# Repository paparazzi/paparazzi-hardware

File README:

#
#   $Id: README 6372 2010-11-07 00:50:29Z esden $
#   Copyright (C) 2004 Pascal Brisset, Antoine Drouin
#
# This file is part of paparazzi.
#
# paparazzi is free software; you can redistribute it and/or modify
# it under the terms of the GNU General Public License as published by
# the Free Software Foundation; either version 2, or (at your option)
# any later version.
#
# paparazzi is distributed in the hope that it will be useful,
# but WITHOUT ANY WARRANTY; without even the implied warranty of
# MERCHANTABILITY or FITNESS FOR A PARTICULAR PURPOSE.  See the
# GNU General Public License for more details.
#
# You should have received a copy of the GNU General Public License
# along with paparazzi; see the file COPYING.  If not, write to
# the Free Software Foundation, 59 Temple Place - Suite 330,
# Boston, MA 02111-1307, USA.  
# 

License:
--------
All PCB CAD files are released under GNU General Public License version 2 or
newer if not stated otherwise.

Older revisions:
----------------
This is a cleaned up repository that does not contain all the history of the
files. For older revisions please check the SVN repository on Savannah:
http://svn.savannah.nongnu.org/viewvc/paparazzi-hardware/trunk/?root=paparazzi

Techno:
-------
PCBs are 4 layers boards.
  They can be ordered from companies like eurocircuits (www.eurocircuits.com).
  I solder the components with a fine temperatue controlled iron. The IMU board 
  contains BGA gyros which will require some sort hot hot air method.

Tools:
  This files are produced using Eagle (www.cadsoft.de) version 4.11 for Linux.
  gerbmerge (http://claymore.engineer.gvsu.edu/~steriana/Python/gerbmerge/) is a
  free gerber panelisation tool. gerbv (http://gerbv.sourceforge.net) is a free
  gerber viewer. eagle3d ( http://www.matwei.de/doku.php?id=en:eagle3d:eagle3d )
  is a tool that allows generation of povray views of the boards.

Outputs:
  We use the eagle batch CAM processor to generate various outputs.
  type "make gerber" to generate gerber.
  type "make printable" to generate postscript and pdf. 
  they will be put in a printable subdirectory in each subdirectory. 

Directory content:
------------------
panel: 
  Contains configuration files used in conjunction with gerbmerge to produce a pannel
  to be sent to the PCB manufacturer (eurocircuits). A panel is a big PCB containing several smaller PCB.
  It allows you to choose which boards you want for your particular system.

controller: 
  This are the paparazzi controller boards.

sensors:

tools:

lib: 
  contains eagle library parts for components not found in the standard eagle library.

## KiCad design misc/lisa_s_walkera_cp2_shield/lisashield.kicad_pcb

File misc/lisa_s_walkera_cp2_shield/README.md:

This is a prototype. Current status:

* Only connectors are used, the rest is cut off.
* No decent GND connection.
* Polarity of tail rotor is reversed, need to exchange wires in the molex-connector.

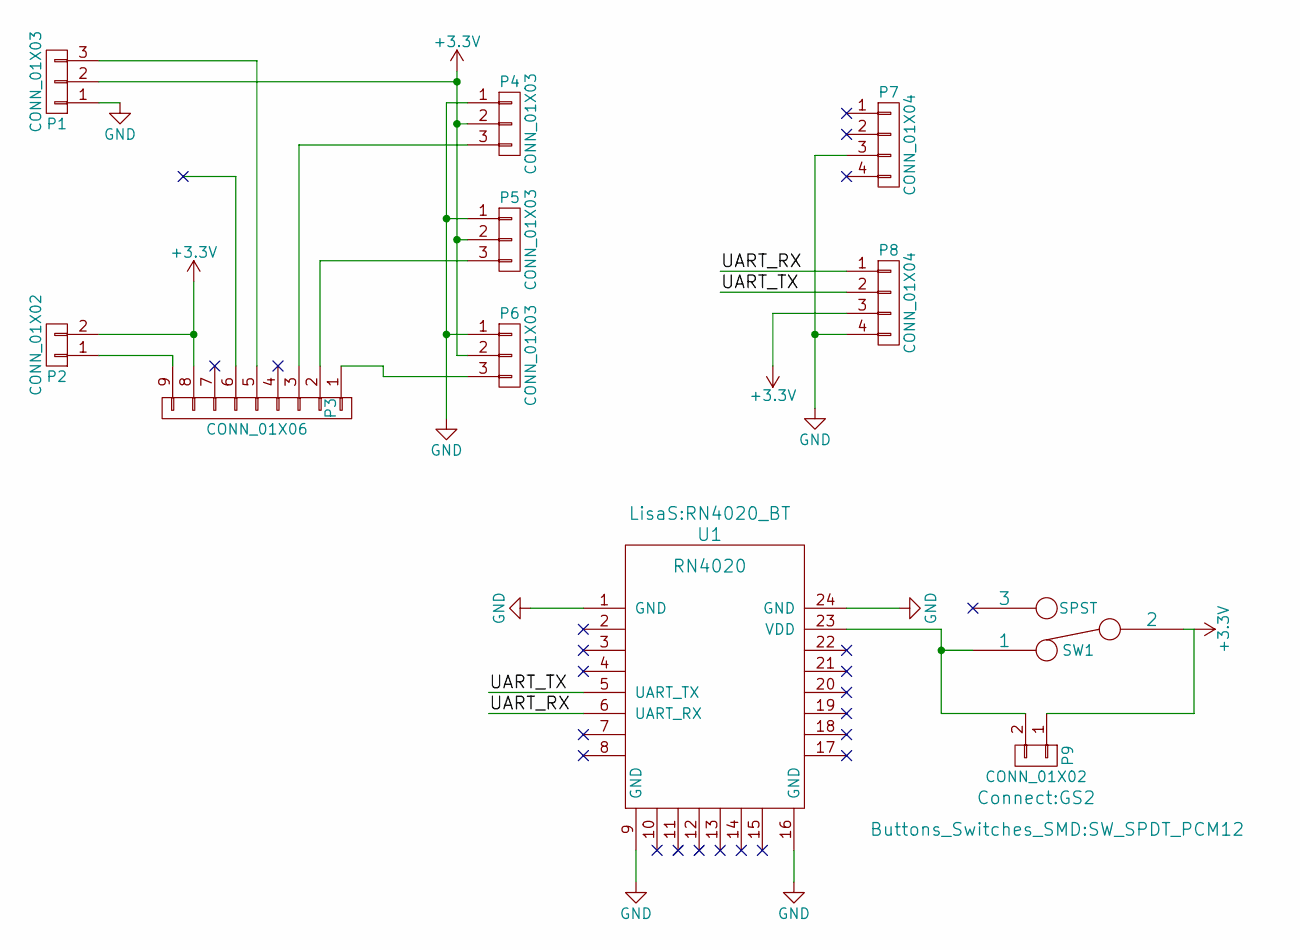
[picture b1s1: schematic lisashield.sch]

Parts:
P1, P4, P5, P6: CONN_01X03; Connector_Molex_PicoBlade_53047-0310
P2: CONN_01X02; Connector_Molex_PicoBlade_53047-0210
P3: CONN_01X06; 9x1_1.27mm
P7, P8: CONN_01X04; 4x1_1.27mm
P9: CONN_01X02; GS2
SW1: SPST; SW_SPDT_PCM12
U1: RN4020; RN4020_BT

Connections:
+3V3: P1.2, P2.2, P3.8, P4.2, P5.2, P6.2, P8.3, P9.1, SW1.2
/UART_RX: P8.1, U1.6 (UART_RX)
/UART_TX: P8.2, U1.5 (UART_TX)
GND: P1.1, P4.1, P5.1, P6.1, P7.3, P8.4, U1.1 (GND), U1.9 (GND), U1.16 (GND), U1.24 (GND)
unnamed: P1.3, P3.5
unnamed: P2.1, P3.9
unnamed: P3.1, P6.3
unnamed: P3.2, P5.3
unnamed: P3.3, P4.3
unnamed: P9.2, SW1.1, U1.23 (VDD)

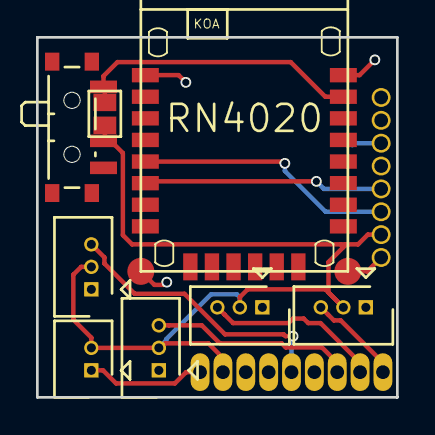
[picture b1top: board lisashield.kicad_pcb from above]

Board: 2 copper layers, 20.0 x 20.0 mm, 11 parts (0 on the bottom side), 10 nets.

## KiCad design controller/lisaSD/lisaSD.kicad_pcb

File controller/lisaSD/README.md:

http://wiki.paparazziuav.org/wiki/SDLogger_SPI_Direct

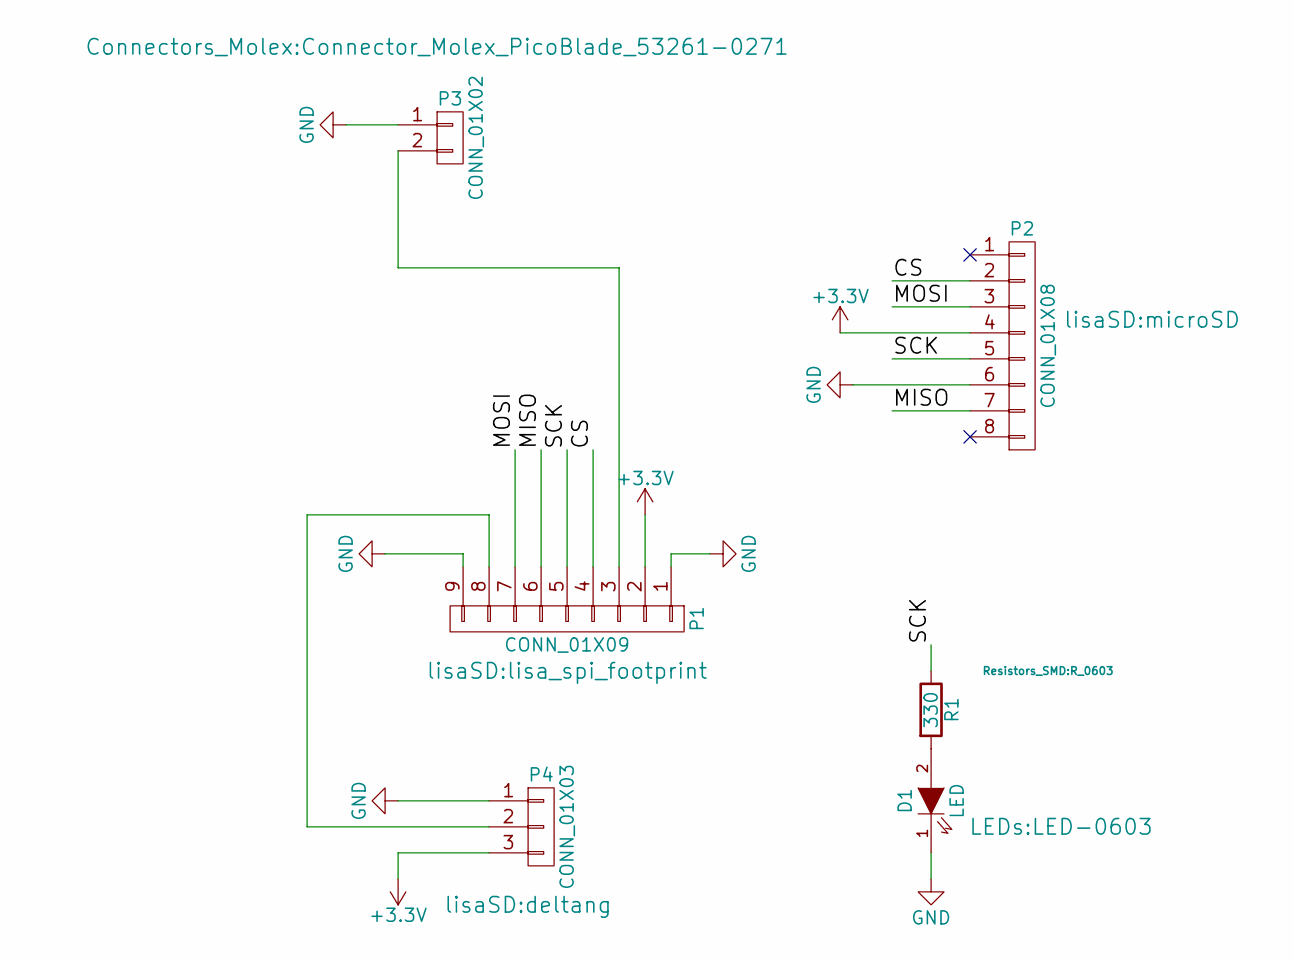
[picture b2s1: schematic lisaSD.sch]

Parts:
D1: LED; LED-0603
P1: CONN_01X09; lisa_spi_footprint
P2: CONN_01X08; microSD
P3: CONN_01X02; Connector_Molex_PicoBlade_53261-0271
P4: CONN_01X03; deltang
R1: 330; R_0603

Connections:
+3V3: P1.2, P2.4, P4.3
/CS: P1.4, P2.2
/MISO: P1.6, P2.7
/MOSI: P1.7, P2.3
/SCK: P1.5, P2.5, R1.1
GND: D1.1 (K), P1.1, P1.9, P2.6, P3.1, P4.1
unnamed: D1.2 (A), R1.2
unnamed: P1.3, P3.2
unnamed: P1.8, P4.2

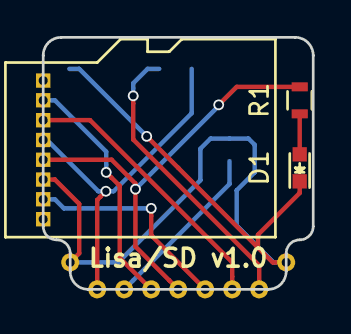
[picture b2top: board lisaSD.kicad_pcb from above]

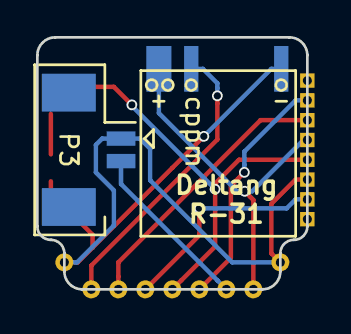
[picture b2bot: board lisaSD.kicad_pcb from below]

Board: 2 copper layers, 15.0 x 14.0 mm, 6 parts (2 on the bottom side), 9 nets.

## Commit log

2011-11-24 Initial commit after a coarce cleanup. For older revisions check the hardware svn repository on Savannah. http://svn.savannah.nongnu.org/viewvc/paparazzi-hardware/trunk/?root=paparazzi
2011-11-24 Reorganized sensor directory a bit.
2011-12-01 Starting work on lia v1.0 controller board.
    It is based on lisa/m and uses throughole 0.1" pin headers instead of
    molex picoblade.
2011-12-01 Added BEC balance inline resistors.
2011-12-02 Improved silkscreen.
2011-12-05 Added castellated hole aspirin footprint.
2011-12-05 Starting revised aspirn v2.1. Added i2c jumpers.
2011-12-05 Added MS5611 to the library.
2011-12-05 Corrected polarity on MS5611 CS pins.
2011-12-05 Added MS5611 to the schematic.
2011-12-05 Removed restrict on MS5611 footprint.
2011-12-05 Added MS5611 to the layout and routed.
2011-12-05 Added pull-ups to local i2c and it is probably a good idea to supply the pressure sensor with power...
    * The i2c pullups are not quoted in any of the mpu-6000 datasheets
    explicitely there is a very unlikely chance that they may not needed.
    Needs to be tested.
    * Connected VDD to +3v3 (seriously no comment ...)
2012-01-12 Updated the population attributes for lia.
2012-01-13 Started Lisa/M V2.1. Swapped the labeling of Analog1 and Analog2 connectors to be more sensible and adhering to the documentation in the wiki. fixes #5
2012-01-13 Swapped labeling of Analog1 and Analog2 connectors to make the naming more sensible.
2012-01-13 Connected the pressure sensor to the MPU-6000. fixes #1
    Now using the auxilary I2C interface instead of the host MCU SPI.
    This will allow reading out of almost all sensor data in one time
    syncronous spi data burst from the MPU-6000.
2012-01-13 Corrected the coordinate system symbol on the silkscreen. fixes #2
2012-01-13 Added DNP attributes to jumpers.
2012-01-13 Increased size of the magnetometer caps to improve performance. fixes #4
    The new size of the HMC magnetometer caps is 0603 otherwise it is
    difficult to get low esr versions of those to gain good performance.
2012-01-16 Some layer cleanup.
2012-01-16 Moved board to origin.
2012-01-16 Added panel rails for lia.
2012-01-17 Approved two remaining drc warnings.
2012-01-17 Generated teardropped version of lia.
2012-01-17 Removed three unnecessary solderstop windows. Fixed solderstop layer comments.
2012-01-17 Added gerber generation files for lia.
2012-01-18 Increased annular rings on lia to 5mil.
2012-01-18 Some more tweaks for DRC satisfaction. Regenerated teardrops.
2012-01-18 Some modifications to satisfy DRC and generated teardropped version.
2012-01-19 Added panel generation to aspirin 2.1.
2012-01-19 Some more DRC improvements.
2012-01-20 Updated bom-ex id designators to be more readable, unique and consistent.
2012-01-20 Updated bom-ex id's to be more consistent, readable and unique.
2012-01-20 Some last minute DRC changes for prototype production run.
2012-01-21 Updated bom-x designators for parts.
2012-01-21 Replaced some blue led's with amber and green ones.
2012-01-23 Changed the resistors for non blue leds to 300ohm.
2012-01-23 Made schematic and brd consistent again.
2012-01-27 More BOM tweaking, also readded the micro USB to lia.
2012-01-27 Minor tweaks to the placement plan.
2012-01-31 Added milling and scoring information.
2012-01-31 Moved vscore 5mil out for better clearence.
2012-01-31 Adjusted horizontal spacing to overlap vscores.
2012-02-01 Removed fiducials on the board, we have them on the rails.
2012-02-01 Added eeprom WP pullup.
2012-02-01 Updated licensing information.
2012-02-01 Updated teardropped aspirin and switched gerber generation to use that instead.
2012-02-01 Added panel rail.
2012-02-01 Added comment about castellated holes.
2012-02-04 Went back to 4layer design. Removed restrict's under the mag and mpu. Removed traces under the MPU based on datasheet recommendations.
2012-02-04 Adding alternative routing of aspirin 2.1. May be a bit cleaner? GYRO_INT and MAG_INT signals are swapped and magnetometer and MPU positions are swapped too.
2012-02-06 Added some more files to gitignore.
2012-02-06 Converted all eagle files to Eagle 6 format.
2012-02-06 Added booz imu v1.2 board files.
2012-02-06 Aspirin alt design is cleaner, made it the official routing of v2.1.
2012-02-06 Switched gerber generation back to non teardropped PCB. As well as changed the panel geometry.
2012-02-06 Reapproved DRC errors.
2012-02-07 Added smaller panel definitions for prototyping purposes.
2012-02-08 Added gtop gps schematic and board files.
2012-02-15 Moved and resized the coordinate system symbol on the silkscreen.
2012-02-15 Moved mag SDA via to connect both sides of the bottom 3V3 plane.
2012-02-16 Some minor cleanups and touchups. Renamed signal silkscreen legend's to better reflect reality.
2012-02-17 Renamed ACC_CS to MPU_CS and changed panel to 3x3.
2012-02-17 Changed via size to 0.4mm.
2012-02-22 Added ublox gps board files.
2012-03-05 Minor final fixes before going into assembly.
2012-03-13 Added SparkFun based xbee carrier with picoblade connector.
2012-03-13 Added gerber generation files for xbee carrier.
2012-03-13 Removed solder stop from vias on the xbee_carrier.
2012-04-03 Added autopilot Tiny v2.11
2012-04-03 Yapa2
2012-04-04 moved Tiny files from v2.1 for v2.11
2012-04-13 Paparazzi Logger (MM/CDW)
2012-05-07 - switched analog1 and analog2 connector labels on schematic and silkscreen - changed LED labels on schematic to be more intuitive and match software defines - changed power led to LEDVIN from LED4 (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
2012-05-07 changed LED labeling to be more intuitive for a user, both on schematic and on silkscreens, also changed power led schematic name to LEDVIN to keep better consistency with silkscreen and remove numbe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
2012-05-07 switched UART1 and UART3 silkscreen labels to be correct
2012-05-07 updated the uart1/3 labeling on silkscreen, unsmashed some LED labels
2012-05-07 Bumped the layer markings to R1.
2012-05-07 Initial commit of lia 1.1.
    Changes from 1.0 to now:
    * Replaced pin header with micro usb connector
    * Rotated top silkscreen labels 180 to show up readable in the quadshot
    airframe.
    * Repositioned the side pinheaders to fit into a breadboard.
    * Removed pressure sensor footprint.
2012-05-10 Added gerber generation scripts to lia v1.1.
2012-05-21 Fixed the corner pin intended for GYRO_CS to be disconnected from ground and labeled RESV on the pcb.
2012-05-21 Added booz imu v1.02
2012-05-23 Added bom-x attributes and connected the tantalum to ground.
2012-06-21 Added a proposal for an improved Aspirin V2.2.
2012-09-28 Added panelization files to aspirin v2.2.
2012-10-01 Minor touchups.
2012-12-04 add external 8x servo board
2013-02-25 Version controlled TWOG_v1.0
2013-03-01 Add I2C multi board
2013-03-02 Add 8x I2C multi connector
2013-03-02 Add Melexis MLX90614 infrared thermometer with I2C interface.
2013-03-02 Add Sensirion SHT75 adapter board for proprietary digital interface
2013-03-12 add SHT2x breakout board
2013-03-12 update SHT75
2013-03-17 small corrections, add pdf schematics: i2c_multi, sht75, mlx90614 and sht25
2013-03-17 add I2C multi adapter
2013-10-18 Updated gerber generation files.
2013-10-18 Updated led footprints to have placement information about orientation.
2013-10-18 Updated aspirin v2.2 to r1
2014-01-30 fix SHT75 humidity board, add 90 degrees version of SHT75 board
2014-04-11 STM32F4 Daughterboard initioal
    Daughterboard for the STM32F4 Discovery, only tht components
2014-04-15 added mouser bom and redme
2014-05-02 fixed align of the main header
    The Main pin header (for the dosvocery board) was offset in the previous
    version.
2015-07-31 added .pro and dxf outline
    Updated with 2015-07-30 6023 on Windows. Added DXF file containing board
    outline + holes. Added KiCAD project file.
2015-09-17 add gps_13 pdf
2016-05-03 SD Logger for Lisa/S
2016-05-04 Added prototype of connector shield Lisa/S with Walkera Genius CPv2
2016-07-05 Updated V2.1 Lisa/M(X) hardware to the final production version.
2016-09-18 Lia breakout board for HITL and testing
2016-09-18 Box for the Lia breakout board
2016-09-18 Lia breakout board (#22)
    * Lia breakout board for HITL and testing
    * Box for the Lia breakout board
2016-09-18 Viking EVCU initial commit
2016-09-18 Viking EVCU initial commit (#23)
2017-02-25 Add 3d-printed damper for Bebop2
2017-03-04 [ecu] Added design files
2017-06-23 fix simple typo
2017-06-23 update typofix
2017-06-24 typo fix (#24)
2017-06-27 decawave arduino
2017-06-27 Lisa-MX-S v1.0
2017-06-27 decawave arduino (#25)
2017-06-27 Lisa-MX-S v1.0 (#26)
